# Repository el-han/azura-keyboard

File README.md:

# The Azura Keyboard

The Azura is a parameterized, split-hand, concave, columnar, ergonomic keyboard: a 3D model of its case, generated in
[Python][] with [build123d][].

Azura builds on and is inspired by the [Dactyl Lynx][] and the wonderful work of its author, David H. Bronke, itself a
rewrite of [the original Dactyl][]. Without them, this keyboard wouldn't exist.

[Dactyl Lynx]: https://github.com/whitelynx/dactyl-lynx-keyboard
[the original Dactyl]: https://github.com/adereth/dactyl-keyboard
[Python]: https://www.python.org/
[build123d]: https://github.com/gumyr/build123d

## The model

* Each half has a finger case whose keys lie on a torus, so the columns and rows both curve around the fingers, and a
  thumb case with its keys on an arc: five thumb keys on the left half, three and a trackball on the right.
* The trackball sits in a cup next to the right thumb keys, with an optical sensor (a [PMW3610 breakout board][])
  below it.
* Every key switch sits on its own small PCB under the key plate.
* The case is printed in two parts per half, a top (key plates and walls) and a bottom (floors and skirt), screwed
  together.

[PMW3610 breakout board]: https://github.com/siderakb/pmw3610-pcb

## Generating the model

### Prerequisites

* [Python][] version 3.12–3.14
* [uv](https://docs.astral.sh/uv/)

### Installing dependencies

```bash
uv sync
```

### Generating

```bash
uv run python -m azura_keyboard
```

This writes STEP files for the case's top and bottom and the combined model of each half to `things/`, plus
models with Cherry MX switches and PCBs in place for checking collisions (not meant for printing). The repository
doesn't contain them: generate them yourself.
The Cherry MX model in `resources/SW_Cherry_MX_Plate.stp` is from [kiswitch](https://github.com/kiswitch/kiswitch)
(MIT / CC-BY-SA 4.0); the DSA keycaps come from the [dsa-keycap](https://github.com/anhthang/dsa-keycap) submodule
(MIT) and the trackball sensor's board from the [pmw3610-pcb](https://github.com/siderakb/pmw3610-pcb)
submodule (CERN-OHL-P v2), so clone with `--recursive` or run `git submodule update --init`.

## Customizing

When customizing your keyboard, you might want to look at API docs for the classes in `azura_keyboard`. You can use `pdoc` for this:
```bash
pdoc -t templates azura_keyboard
```

## License

Copyright © 2015-2024 Matthew Adereth and David H. Bronke  
Copyright © 2026 Hannes Ellinger

The source code for generating the models (everything excluding the generated `things/` and the [resources/](resources/) directories) is distributed under the [GNU AFFERO GENERAL PUBLIC LICENSE Version 3](LICENSE).  The generated models and PCB designs are distributed under the [Creative Commons Attribution-ShareAlike License Version 4.0](LICENSE-models).

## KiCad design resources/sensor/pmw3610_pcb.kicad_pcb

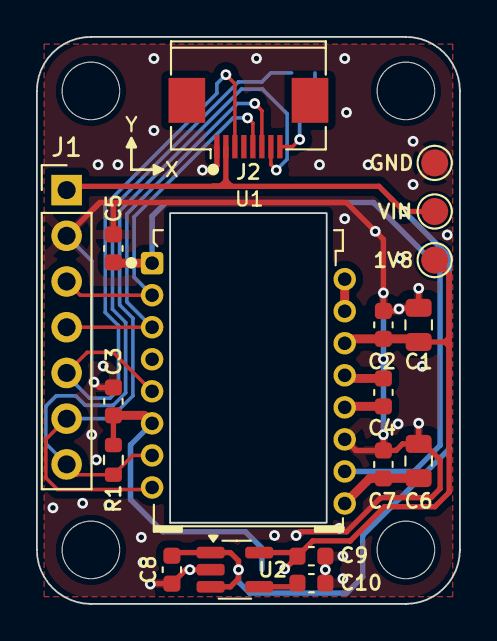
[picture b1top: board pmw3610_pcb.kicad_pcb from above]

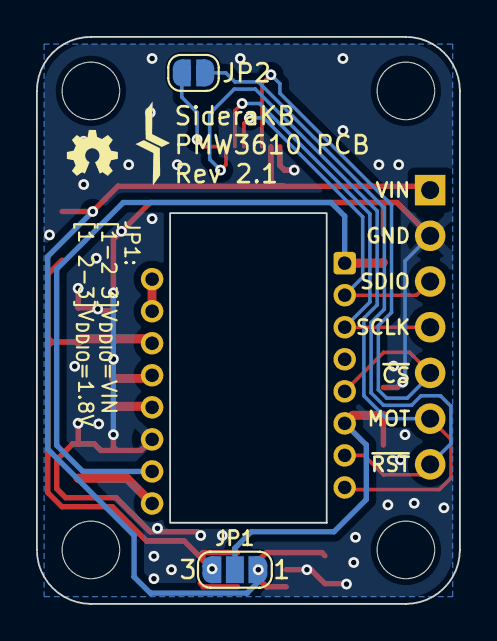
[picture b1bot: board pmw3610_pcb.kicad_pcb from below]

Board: 2 copper layers, 23.5 x 31.5 mm, 24 parts (6 on the bottom side), 16 nets.

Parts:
C1: 3.3uF/16V; C_0805_2012Metric
C2, C3, C4: 100nF; C_0603_1608Metric
C5, C7: 10nF; C_0603_1608Metric
C6: 10uF; C_0805_2012Metric
C8, C9: 1uF; C_0603_1608Metric
C10: 22nF; C_0603_1608Metric
H1, H2, H3, H4: MountingHole; MountingHole_3.2mm_M3_ISO14580
J1: Conn_PinHeader; PinHeader_1x07_P2.54mm_Vertical
J2: Conn_FPC; FPC_8P_0.5mm_AFC01-S08FCA-00
JP1: SolderJumper_3_Open; SolderJumper-3_P1.3mm_Open_RoundedPad1.0x1.5mm_NumberLabels
JP2: FPC_RST; SolderJumper-2_P1.3mm_Open_RoundedPad1.0x1.5mm
R1: 10k; R_0603_1608Metric
TP1, TP2, TP3: TestPoint; TestPoint_Pad_D1.5mm
U1: PMW3610; PMW3610DM-SUDU 16Pin
U2: TLV74318PDBVR; SOT-23-5_HandSoldering

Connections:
+1V8: C1.1, C2.1, C9.1, JP1.3 (B), TP3.1, U1.14 (VDD), U2.5 (OUT)
GND: C1.2, C2.2, C3.2, C5.2, C6.2, C7.2, C8.2, C9.2, C10.2, J1.2, J2.1, TP1.1, U1.11 (GND), U2.2 (GND)
MOTION: J1.6, J2.7, U1.8 (MOTION)
unnamed: J2.8, JP2.2 (B)
unnamed: C5.1, U1.1 (+VCSEL), U1.10 (PASS_T)
unnamed: U1.15 (XYLASER), U1.16 (-VCSEL)
unnamed: C4.2, U1.13 (CN)
unnamed: C4.1, U1.12 (CP)
unnamed: C6.1, C7.1, U1.9 (VCP)
unnamed: C10.1, U2.4 (NC)
SCLK: J1.4, J2.6, U1.3 (SCLK)
SDIO: J1.3, J2.5, U1.2 (SDIO)
VDDIO: C3.1, JP1.2 (C), R1.1, U1.6 (VDDIO)
VIN: C8.1, J1.1, J2.2, JP1.1 (A), TP2.1, U2.1 (IN), U2.3 (EN)
nCS: J1.5, J2.3, U1.5 (NCS)
nRESET: J1.7, JP2.1 (A), R1.2, U1.7 (NRESET)

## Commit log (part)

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2020-11-22 fix(resources):‌ added missing preview.png
2020-11-22 feat(dactyl.clj): removed old bottom pieces, added new board mounts, added different color to preview model
2020-11-22 fix(dactyl.clj): fixed mount post position for bare boards; split preview into its own def
2020-11-22 feat(README.md):‌ more detail, and links
2020-11-22 feat(dactyl.clj): reworked board positioning, and added rubber foot attachment points
2020-11-22 feat(dactyl.clj): TRRS jack placeholder for preview
2020-11-22 feat(dactyl.clj):‌ remove unnecessary dactyl-top-left-with-teensy.scad
2020-11-22 fix(project.clj): corrected :license to match the actual license of the project
2020-11-22 feat(things): updated pregenerated models
2020-11-22 fix(dactyl.clj): corrected color on TRRS connector, and updated preview
2020-11-22 feat(README.md):‌ link to a list of places to get Ergodox keycap sets
2020-11-24 feat(README.md):‌ added future plans
2020-11-24 feat(README.md):‌ added mention of plans to add user-defined switchable keymaps to replace Orbweaver
2020-11-26 feat(qmk-guide): updated my layout
2020-11-27 feat(dactyl.clj):‌ implemented backplates for Cherry MX sockets
    Also, cleaned up naming and added some other model outputs for verification.
2020-11-27 feat(README.md):‌ we now have hot-swap socket support
2020-11-28 feat(dactyl.clj): added TrackPoint mounting
2020-11-30 feat(dactyl.clj): reworked board mounts and positioning
    Should be much easier to mount now.
2020-12-05 feat(circuits): added KiCad schematic
2020-12-05 feat(dactyl.clj): added support for HiLetgo STM32F103C8T6 board
2020-12-06 feat(circuits): added Proton C version of the schematic
2020-12-11 fix(dactyl.clj): boards were upside down!
    Foot supports are a bit thin now, though.
2020-12-15 feat(dactyl.clj): added notches for clips on MX-style switches
    Copied from https://github.com/whitelynx/parametric-key-tester
2021-01-02 Expanded BOM
2021-01-03 feat(dactyl.clj): added new separate `cherry-plate-with-key-mount-and-backplate` key plate def
2021-01-03 fix(things): removed invalid exec permissions
2021-01-30 feat(dactyl.clj): added basic TrackPoint mouse frame
2021-01-30 fix(dactyl.clj): added clearance behind top thumb switch so the connections fit
2021-01-31 feat(dactyl.clj): tweaked TrackPoint mount thickness and improved TrackPoint mouse
2021-02-10 feat(dactyl.clj): reinforce board mount post, and adjust Pro Micro size for clearance
2021-02-13 feat(README.md):‌ updated copyright
2021-02-15 feat(dactyl.clj): tweak TrackPoint mount
2021-03-07 feat(dactyl.clj):‌ flatten top of inside cavity, and optimize board mount for ease of printing
    Also, remove unused `post-wall-thickness` var.
2021-03-16 feat(dactyl.clj):‌ fixed trackpoint mouse dimensions, tweaked pro micro board size
2021-03-16 feat(dactyl.clj): tweak thumb cluster position and orientation
2021-04-09 feat(dactyl.clj):‌ tweaked board mounts
2021-04-09 fix(dactyl.clj): correct foot indent
2021-04-09 feat(dactyl.clj): added more to the board mount so it doesn't need supports
2021-04-15 feat(dactyl.clj):‌ added a 6th key to the thumb cluster, and fixed most of the thumb walls
2021-04-15 feat(dactyl.clj): remove web between thumb and main board to make it easier to wire
2021-04-16 feat(dactyl.clj): reinforce USB port opening at the end of the board
2021-04-16 feat(dactyl.clj): remove end bumps on board mount posts so things fit easier
2021-04-17 feat(dactyl.clj): add border around top ("left") of thumb cluster
2021-04-17 feat(dactyl.clj): remove confusing `place` aliases
2021-04-17 feat(dactyl.clj): round corner of thumb cluster for comfort
2021-04-24 feat(circuits): added a 2-axis joystick component
2021-04-24 feat(README.md):‌ added Arduino Micro as recommended microcontroller
2023-07-25 Corrected QMK documentation links in README.md
2023-08-22 Adjusted microcontroller recommendation
2023-08-22 Use black-pill board for building!
2023-08-22 Thickened stabilizer cutouts so they don't leave paper-thin surfaces behind
    Also, improved comments about keycaps.
2023-08-22 Mirror key holes correctly when mirroring the whole case, so that the switch contacts still line up
2023-08-22 Added clearance for hotswap socket on backplate in thumb cluster
2023-09-28 Added new Python-based dactyl_lynx design based on spkb
2024-01-04 Tweaked finger well tenting nut positions and added thumb cluster tenting nuts
2024-01-04 Updated README.md with Python-based instructions
2024-01-04 Updated bill of materials in README.md
2024-01-04 Fixed imports for latest SolidPython2 changes
2024-01-05 Added photo of new skeleton prototype
2024-01-13 Moved assembly into a separate KeyboardAssembly class
    instead of directly in the __main__ section
2024-01-24 Rotate thumb cluster by 10 degrees around (1,1,1), and use thumb layout placement for thumb nuts
2024-01-27 added mention of Apple Magic Mouse scroll ball
2024-01-28 Added option for generating the bottom nuts on the thumb cluster, disabled by default
2024-01-28 updated keycaps info, and updated image URLs
2024-01-31 removed old Clojure-centric README sections and updated copyright
2024-01-31 Updated skeleton-prototype.jpg
2024-02-04 README: added initial draft of the Wiring section
2024-02-12 tweaked thumb cluster position
2024-02-12 tweaked thumb cluster position, board mount position, and middle/pinky column positions
2024-02-12 README: fix table and list formatting
2024-02-12 Added 4-pin mini-DIN pinout for connecting the two sides
2024-02-12 Added placement adjustment to move the 2u thumb key up so it's easier to press
2024-02-14 Updated dependencies
    Specifically, spkb needed to be updated so we could use the improved switch clip notches.
2024-02-28 README: add note about wiring color mismatch in photos
    Note: still need those photos added
2024-02-28 Steeper incline for finger wells, and repositioning Mini-DIN connector to be placed based on adjacent key position
2024-03-02 Tweaked thumb cluster positioning so I can comfortably use it
2024-05-01 Adjusted board position
2024-07-02 Reworked Mini-DIN connector mount to be more robust
2024-07-02 Shifted LCD mount to fit latest design changes
2024-07-02 Added single-piece frame (finger and thumb wells combined)
2024-11-05 fix(dactyl_lynx): minor tweaks to board mount
2024-11-05 update(things): updated with latest rendered .scad and .stl models
2024-11-05 README: updated note about keyswitch plates
2024-11-05 fix(dactyl_lynx): added compensation for different socket wall thicknesses
    and instructions for using different socket shapes
2024-11-05 feat(dactyl_lynx): render single-key PCBs in the combined model
2024-11-06 fix(dactyl_lynx): fix some clearance issues when using single-key PCBs
2024-11-06 tweak(dactyl_lynx): tweaked colors and added keycaps back to the combined model
2024-11-06 update(things): re-rendered .stl outputs with `predictible-output`
2024-11-07 feat(dactyl_lynx): started adding back cover
2024-11-07 fix(dactyl_lynx): fix trackpoint_shape() to actually run, and corrected positioning and number of segments of sphere
2024-11-07 feat(dactyl_lynx): output bottom covers separately
2024-11-08 update(README.md): added magnets to BOM
2024-11-09 update(README.md): added TrackPoint, single-keyswitch PCB support, and new RMK-based firmware to the list of changes
    Also updated note about Vial's layer limitations.
2024-11-09 fix(README.md): Rust, not Ruby
    ...now I need to go check if I made that slip-up anywhere else.
2024-11-11 fix(dactyl_lynx): exclude the correct thumb key position
    so we don't end up with a random piece of web sticking out the bottom
2024-11-12 fix(dactyl_lynx): subtract cover magnet holes again so we don't fill one of the attachment holes
2024-11-13 feat(dactyl_lynx): added feet for the bottom cover
2024-11-13 update(things): added .scad and .stl outputs for bottom cover with feet
2024-11-15 update(README.md): I've been keeping the models in things/ up to date, so it's OK to use them
2024-11-16 feat(dactyl_lynx): moved logic for combined assembly into separate build_combined_output() function
2024-11-16 feat(dactyl_lynx): corrected argparse app description
2024-11-17 fix(dactyl_lynx): fix some issues raised by pyright
2024-11-17 update(dactyl_lynx_keyboard): split generation code into separate modules
2024-11-22 tweak(dactyl_lynx): moved build_combined_output up
2024-11-25 update(things): re-rendered OpenSCAD outputs
2024-11-25 feat(dactyl_lynx_keyboard.dactyl_lynx): added deep dish homing keys
2024-11-25 feat(dactyl_lynx_keyboard.dactyl_lynx): color keycaps in the switch_cap() function
2024-11-25 feat(dactyl_lynx_keyboard.dactyl_lynx): add etch_key_positions option
2024-11-25 feat(dactyl_lynx_keyboard.assembly): added enable_trackpoint and enable_nuts properties
2024-11-25 fix(dactyl_lynx_keyboard.assembly): corrected enable_nuts logic
2024-11-26 feat(things): added {left,right}_finger_bottom_cover_with_nuts renders
2024-11-26 cleanup(dactyl_lynx_keyboard.layouts.layout): removed unused Layout.caps()
    Use Layout.place_all(keycap_shape) instead.
2024-11-26 feat(dactyl_lynx_keyboar.layouts.layout): added type annotations
2024-11-26 feat(dactyl_lynx_keyboar.layouts.thumb_well): added type annotations
2024-11-26 feat(dactyl_lynx_keyboard.layouts): added size_adjust and position_adjust callbacks to all Layout.web_*() methods
2024-11-27 feat(dactyl_lynx_keyboard.layouts): pass through size_adjust and position_adjust
2024-11-27 feat(dactyl_lynx_keyboard.assembly): adjust bottom cover pieces to make more room around tight clearances
    Involves using size_adjust and position_adjust, and correctly resizing/placing bottom cover pieces based on those.
2024-11-27 feat(dactyl_lynx_keyboard.dactyl_lynx): reworked keycap legends to give more options and place them correctly
2024-11-27 update(resources/preview.png): re-rendered using POV-Ray
2024-11-27 feat(README.md): added instructions for exporting to STL and rendering images
2024-11-27 feat(dactyl_lynx_keyboard.dactyl_lynx): adjusted colors to make the POV-Ray render look more accurate
2024-11-27 chore: remove outdated KiCad projects
2024-12-01 feat(dactyl_lynx_keyboard.assembly): correct magnet position in top outer corner to not interfere with bolts
2024-12-01 update(things): re-rendered SCAD and STL outputs
2024-12-08 feat(README.md): updated instructions for latest OpenSCAD fixes
2024-12-09 task: switched from pipenv to poetry
2024-12-09 feat(README.md): added instructions for viewing API docs
2024-12-09 feat: render README.md in pdoc, and switch from _ to * in README.md so it renders correctly in pdoc
2024-12-10 feat(dactyl_lynx_keyboard.layouts): added more docstrings and type annotations
2024-12-11 update(things): re-rendered OpenSCAD and STL outputs
2024-12-16 feat(dactyl_lynx_keyboard.assembly): subtract simplified PCB shapes with some small margin
    to make sure there's enough room to mount PCBs.
2024-12-16 feat(dactyl_lynx_keyboard): moved colors for "combined" model into a config structure, and switched to use Keyswitch.switch() instead of mx_keyswitch()
2024-12-16 feat: added scripts/render-stls.sh
2024-12-17 feat(dactyl_lynx_keyboard.assembly): made tripod mount much more robust
2024-12-17 fix(dactyl_lynx_keyboard): fixed typing issues and improved a docstring
2024-12-17 feat(dactyl_lynx_keyboard.layouts): use base class generate_positions(), and added positions_to_skip
2024-12-19 feat(dactyl_lynx_keyboard): tweaked board mount position, using key_place for it
    Also, added cutout to bottom cover to make sure we have sufficient space for wires.
2024-12-21 feat(dactyl_lynx_keyboard.assembly): added new _with_tripod_mount and renamed existing one to _with_t_nut
    Now using a different part for the 1/4"-20 threads.
2024-12-21 update(things): re-rendered OpenSCAD, STL, and POVray outputs
2026-01-28 no thin walls, new thumb cluster design

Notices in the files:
resources/sensor/pmw3610_pcb.kicad_pcb:
Open Source Hardware, CERN-OHL-P v2
